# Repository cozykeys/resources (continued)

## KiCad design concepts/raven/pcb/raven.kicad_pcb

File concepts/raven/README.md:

# CozyKeys Raven

This repository contains the design files for the CozyKeys Raven, a 63-key
ergonomic mechanical keyboard.

This keyboard is still a work in progress.

## Build Notes

- For switch LEDs, the longer leg goes in the '+' hole.
- For switch LED resistors, use:
    -

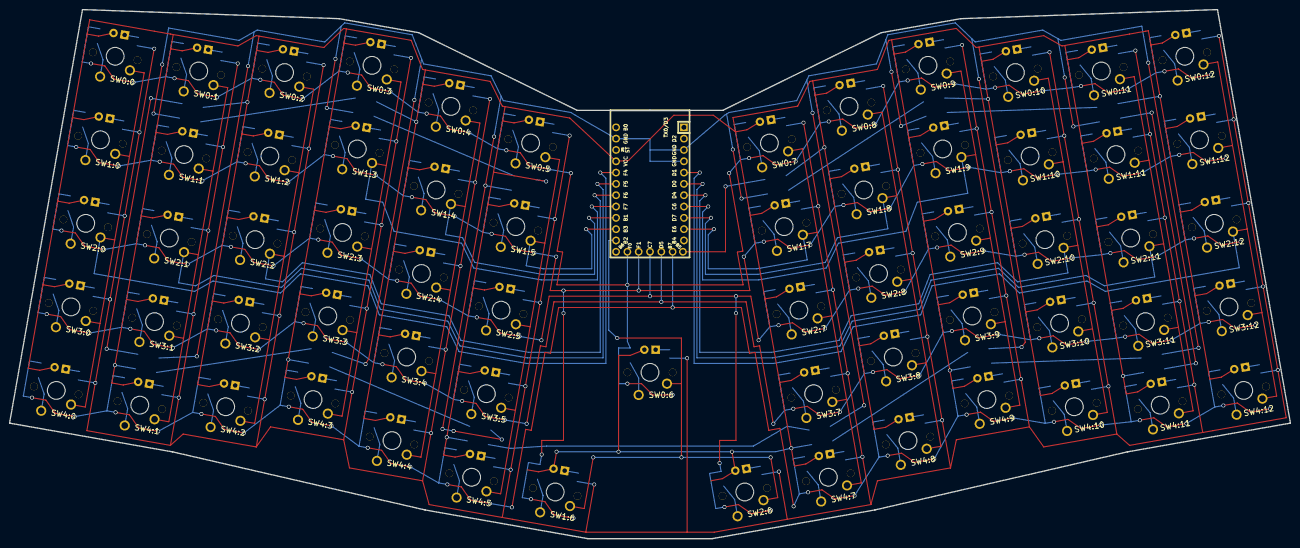
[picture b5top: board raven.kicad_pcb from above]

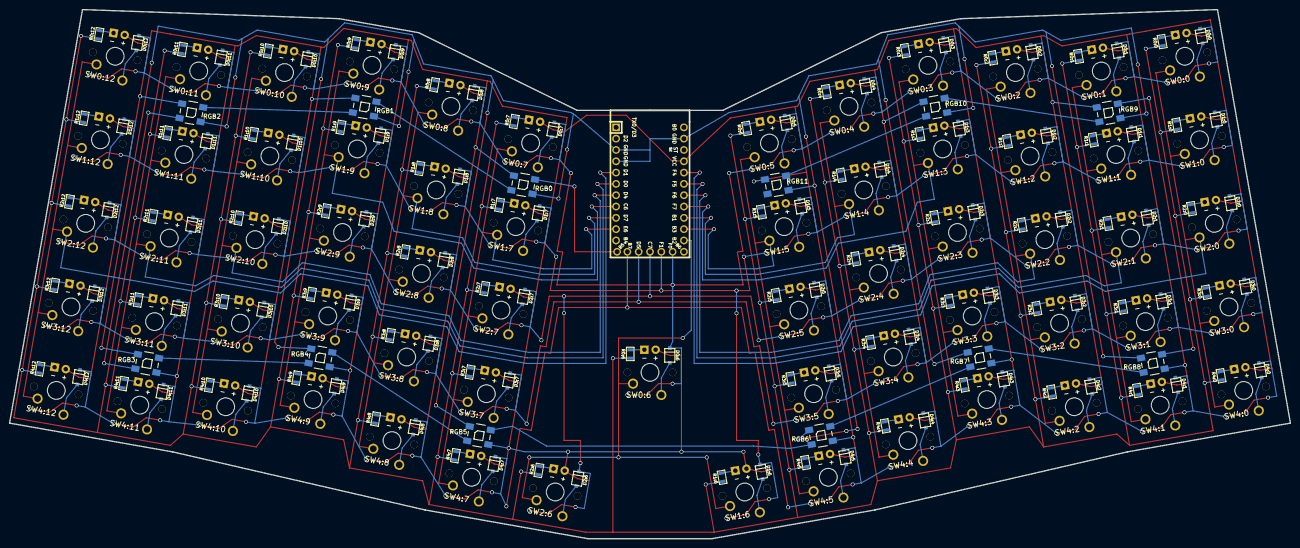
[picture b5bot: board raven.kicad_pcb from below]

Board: 2 copper layers, 287.6 x 118.8 mm, 13 parts (13 on the bottom side), 14 nets.

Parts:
RGB0, RGB1, RGB2, RGB3, RGB4, RGB5, RGB6, RGB7, RGB8, RGB9, RGB10, RGB11: VAL**; WS2812B
U1: Elite-C

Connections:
unnamed: RGB0.3, RGB1.3, RGB2.3, RGB3.3, RGB4.3, RGB5.3, RGB6.3, RGB7.3, RGB8.3, RGB9.3, RGB10.3, RGB11.3, U1.21
N-GND-0: RGB0.1, RGB1.1, RGB2.1, RGB3.1, RGB4.1, RGB5.1, RGB6.1, RGB7.1, RGB8.1, RGB9.1, RGB10.1, RGB11.1, U1.3, U1.4, U1.23
N-RGB-D0: RGB0.2, U1.12
N-RGB-D1: RGB0.4, RGB1.2
N-RGB-D2: RGB1.4, RGB2.2
N-RGB-D3: RGB2.4, RGB3.2
N-RGB-D4: RGB3.4, RGB4.2
N-RGB-D5: RGB4.4, RGB5.2
N-RGB-D6: RGB5.4, RGB6.2
N-RGB-D7: RGB6.4, RGB7.2
N-RGB-D8: RGB7.4, RGB8.2
N-RGB-D9: RGB8.4, RGB9.2
N-RGB-D10: RGB9.4, RGB10.2
N-RGB-D11: RGB10.4, RGB11.2

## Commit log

2018-07-23 Working on PCB generation
2018-07-23 More PCB generation work
2018-11-25 Pcb gen (#1)
2019-03-19 Allow constants in path components
2019-03-19 Move kbmath into kbutil solution
2019-03-19 Fix publishing in makefile
2019-03-23 Add more styling support
2019-03-23 Fix style deserialization
2019-03-25 Changes to support bloomer rev4
2019-04-26 Improve legend SVG generation
2019-08-03 Improve build directory structure
2019-08-04 Add bearing generation command to kbutil
2019-08-04 Add bearing generation command to kbutil (#2)
2019-08-05 Radix PCB generation support
2019-08-05 Add initial Radix PCB generation support (#3)
2019-08-05 Update Radix PCB edge cuts
2019-08-06 Add publish output path
2019-08-10 Clean up build output paths
2019-08-13 Round key bearings to 3 digits
2019-08-15 Add generic text rendering support
2019-08-15 Support setting svg viewbox size
2019-10-14 Add keycap outline to MX footprint template
2019-10-18 Add vector projection and fix unit tests
2019-10-18 Update scratchpad
2019-10-19 Add path fill opacity support
2019-10-20 Raven support
2019-10-21 Work on Raven RGB traces
2020-02-10 Add rounding to vectors/curves
2020-02-10 Updates (#4)
2020-02-12 Updates for bloomer v4
2020-02-13 Bloomer progress
2020-02-14 Don't needlessly cast
2020-02-14 Add support for Visibility attribute
2020-03-13 Layer squashing
2020-09-11 Cleanup path writer class
2020-09-18 Fix default style for circles
2020-10-02 Remove useless extended help text
2020-10-02 Remove useless extended help text (#5)
2020-10-02 Add description to debug-svg option
2020-10-02 Add description to debug-svg option (#6)
2020-10-05 Add concepts readme
2020-10-05 Add guide for creating kicad modules
2020-10-05 Merge cozykeys repos (#7)
    * Merge cozykeys repos
    * Update README.md
    * Add concepts readme
2020-10-15 Add guide for finalizing images
2020-10-20 Add script for finalizing image files
2020-10-21 Add WIP doc for how keyboards work
2021-03-23 Add assets
2021-04-07 Initial commit of kbutil-go
2021-04-07 Progress on kbutil-go
2021-11-06 Rename guides dir to docs
2021-11-08 Add kicad setup doc
2021-11-19 Bump dotnet version
2021-11-19 Add Row/Column to keys
2021-11-20 Initial move
2021-11-20 Replace KbMath with KbUtil
2021-11-20 Get solution to build/run
2021-11-20 Remove unnecessary commands
2021-11-20 Merge KbMath utilities into KbUtil (#9)
    * Initial move
    * Replace KbMath with KbUtil
    * Get solution to build/run
    * Remove unnecessary commands
2021-11-24 Add centered B3F-10 tactile switch footprint
2021-12-17 Move triad into this repo
2022-03-30 Finish implementing expand-vertices2 command
2022-03-30 Start experimenting with XML unmarshalling
2022-03-31 Progress
2022-04-01 Progess
2022-05-03 Initial commit of kbutil port to go (#10)
2022-12-08 Bump Newtonsoft.Json from 13.0.1 to 13.0.2 in /kbutil/src/KbUtil.Console
    Bumps [Newtonsoft.Json](https://github.com/JamesNK/Newtonsoft.Json) from 13.0.1 to 13.0.2.
    - [Release notes](https://github.com/JamesNK/Newtonsoft.Json/releases)
    - [Commits](https://github.com/JamesNK/Newtonsoft.Json/compare/13.0.1...13.0.2)
    ---
    updated-dependencies:
    - dependency-name: Newtonsoft.Json
2022-12-08 Bump Newtonsoft.Json from 13.0.1 to 13.0.2 in /kbutil/src/KbUtil.Lib
    Bumps [Newtonsoft.Json](https://github.com/JamesNK/Newtonsoft.Json) from 13.0.1 to 13.0.2.
    - [Release notes](https://github.com/JamesNK/Newtonsoft.Json/releases)
    - [Commits](https://github.com/JamesNK/Newtonsoft.Json/compare/13.0.1...13.0.2)
    ---
    updated-dependencies:
    - dependency-name: Newtonsoft.Json
2024-02-10 Start prototyping new keyboard
2024-10-22 Add image without logo
2024-12-21 Saving local changes
    I don't remember when I worked on this or what I was doing. These
    changes may even be bad or WIP but I'm committing them to avoid any
    unsaved local changes that could get lost.
